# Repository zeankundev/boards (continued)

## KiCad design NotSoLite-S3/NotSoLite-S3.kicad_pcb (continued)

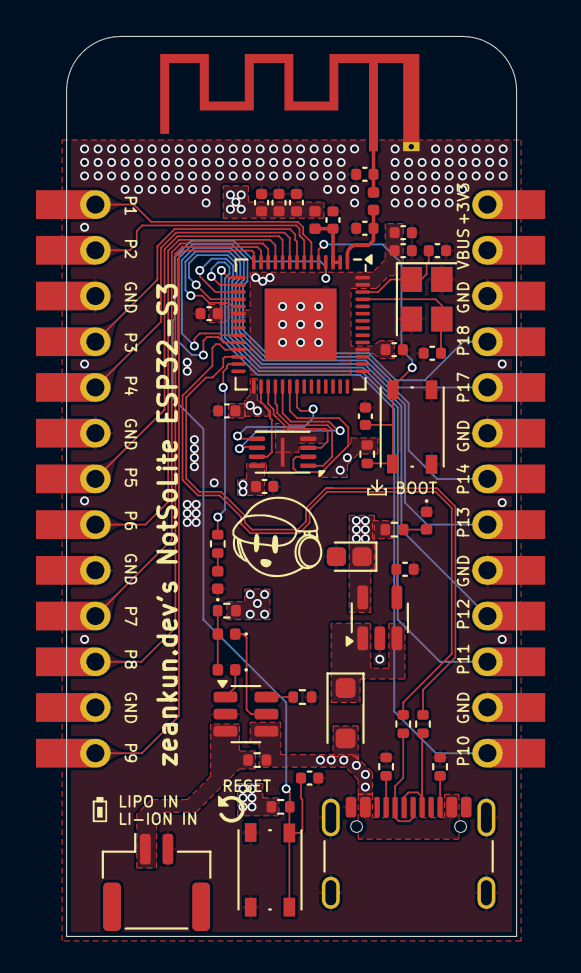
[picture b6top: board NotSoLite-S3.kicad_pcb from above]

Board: 6 copper layers, 25.0 x 50.0 mm, 48 parts (1 on the bottom side), 49 nets.

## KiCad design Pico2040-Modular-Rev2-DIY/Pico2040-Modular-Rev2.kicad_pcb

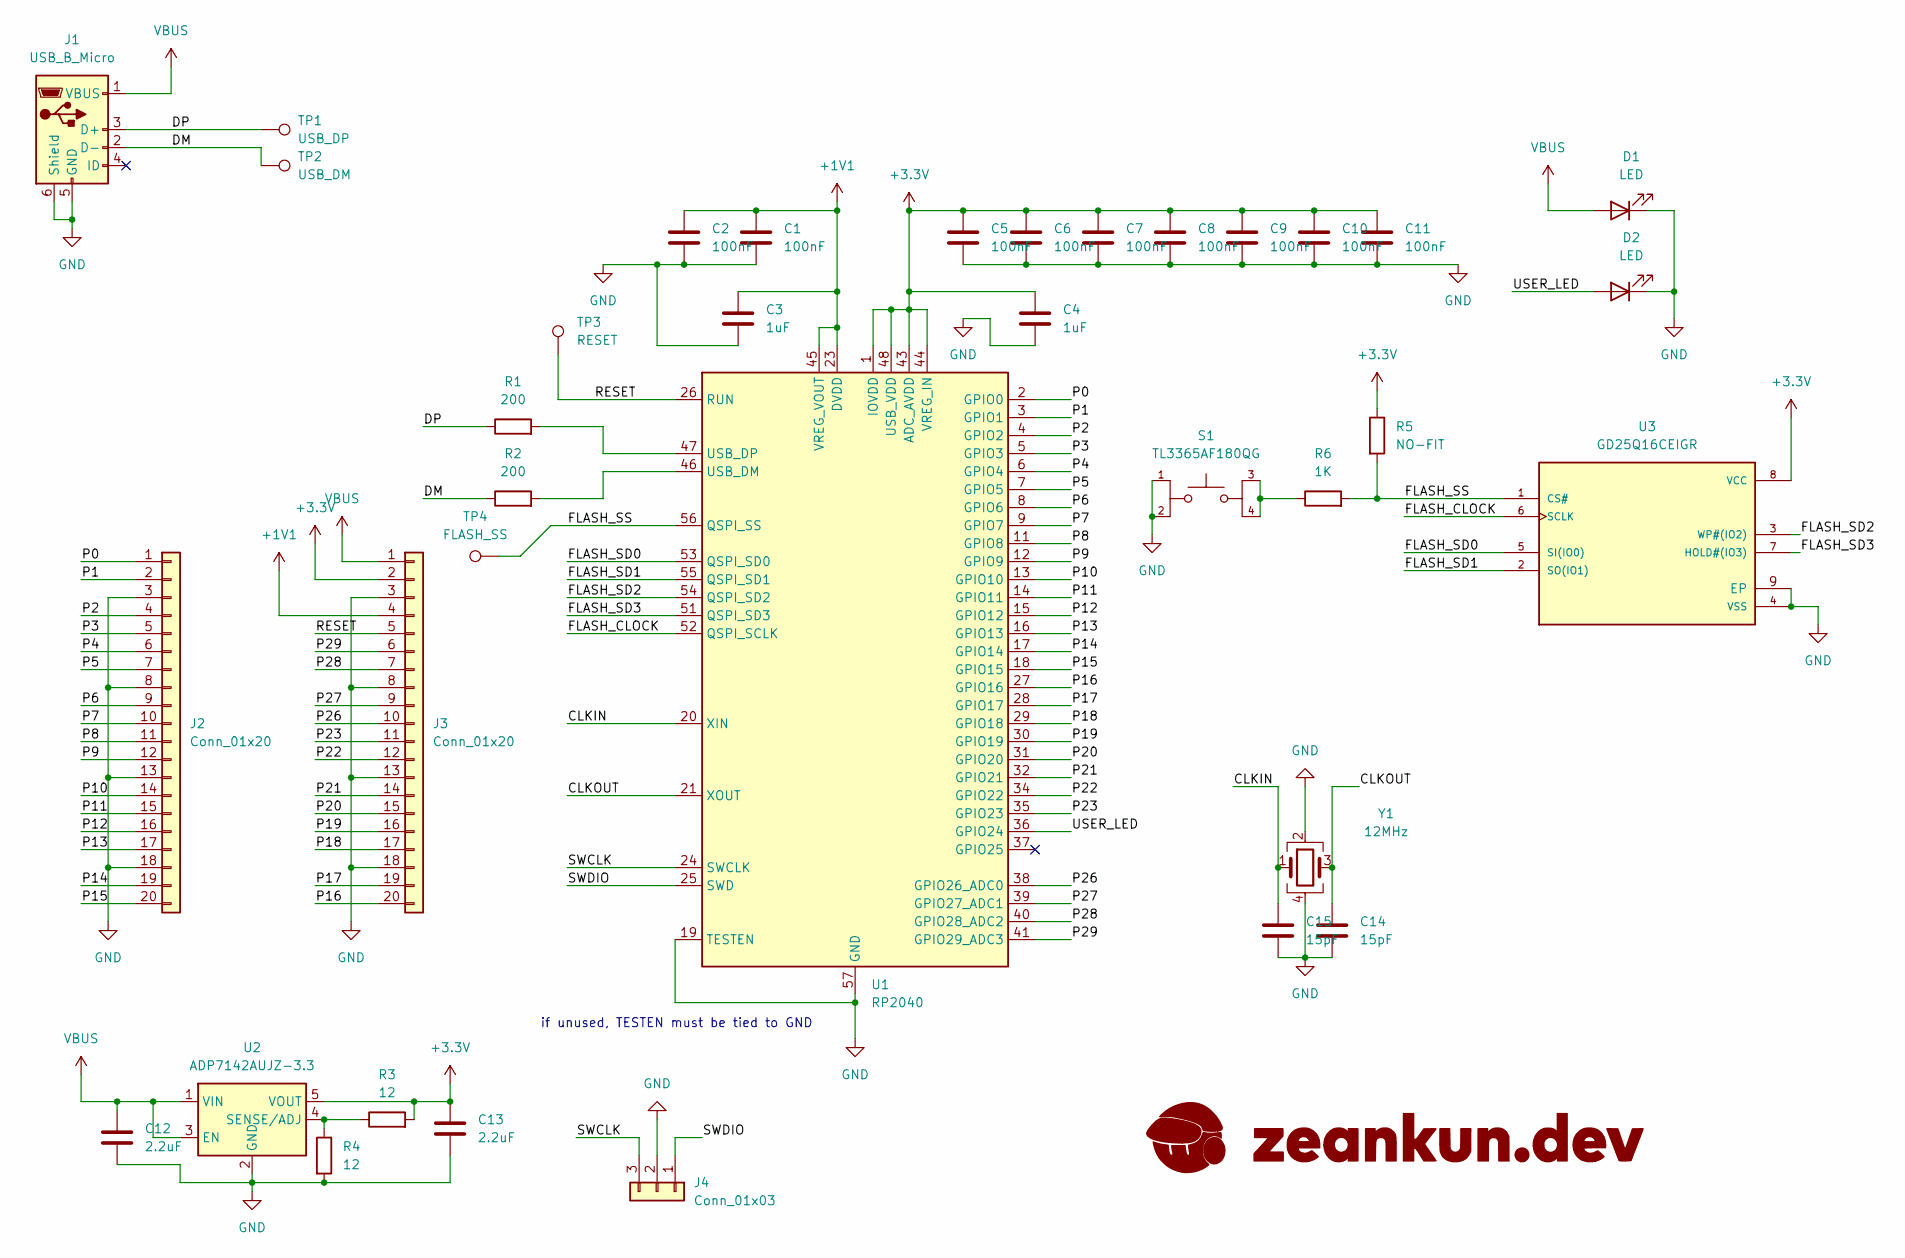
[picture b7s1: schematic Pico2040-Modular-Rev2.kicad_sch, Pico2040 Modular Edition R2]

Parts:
C1, C2, C5, C6, C7, C8, C9, C10, C11: 100nF; C_0201_0603Metric
C3, C4: 1uF; C_0201_0603Metric
C12, C13: 2.2uF; C_0201_0603Metric
C14, C15: 15pF; C_0201_0603Metric
D1, D2: LED; LED_0201_0603Metric
J1: USB_B_Micro; USB_Micro-B_Amphenol_10103594-0001LF_Horizontal
J2, J3: Conn_01x20; PinHeader_1x20_2H_P2.54mm_Vertical
J4: Conn_01x03; PinHeader_1x03_P2.54mm_Vertical
R1, R2: 200; R_0201_0603Metric
R3, R4: 12; R_0201_0603Metric
R5: NO-FIT; R_0201_0603Metric
R6: 1K; R_0201_0603Metric
S1: TL3365AF180QG; SW_TL3365AF180QG; PARTREV A
TP1: USB_DP; TestPoint_Pad_D1.0mm
TP2: USB_DM; TestPoint_Pad_D1.0mm
TP3: RESET; TestPoint_Pad_D1.0mm
TP4: FLASH_SS; TestPoint_Pad_D1.0mm
U1: RP2040; QFN-56-1EP_7x7mm_P0.4mm_EP3.2x3.2mm
U2: ADP7142AUJZ-3.3; TSOT-23-5
U3: GD25Q16CEIGR; PSON50P200X300X50-9N; PARTREV 3.0
Y1: 12MHz; Crystal_SMD_2520-4Pin_2.5x2.0mm

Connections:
+1V1: C1.1, C2.1, C3.1, J3.4, U1.23 (DVDD), U1.45 (VREG_VOUT), U1.50 (DVDD)
+3.3V: C4.1, C5.1, C6.1, C7.1, C8.1, C9.1, C10.1, C11.1, C13.1, J3.2, R3.2, R5.1, U1.1 (IOVDD), U1.10 (IOVDD), U1.22 (IOVDD), U1.33 (IOVDD), U1.42 (IOVDD), U1.43 (ADC_AVDD), U1.44 (VREG_IN), U1.48 (USB_VDD), U1.49 (IOVDD), U2.5 (VOUT), U3.8 (VCC)
/CLKIN: C15.1, U1.20 (XIN), Y1.1
/CLKOUT: C14.1, U1.21 (XOUT), Y1.3
/DM: J1.2 (D-), R2.1, TP2.1
/DP: J1.3 (D+), R1.1, TP1.1
/FLASH_CLOCK: U1.52 (QSPI_SCLK), U3.6 (SCLK)
/FLASH_SD0: U1.53 (QSPI_SD0), U3.5 (SI(IO0))
/FLASH_SD1: U1.55 (QSPI_SD1), U3.2 (SO(IO1))
/FLASH_SD2: U1.54 (QSPI_SD2), U3.3 (WP#(IO2))
/FLASH_SD3: U1.51 (QSPI_SD3), U3.7 (HOLD#(IO3))
/FLASH_SS: R5.2, R6.2, TP4.1, U1.56 (QSPI_SS), U3.1 (CS#)
/P0: J2.1, U1.2 (GPIO0)
/P1: J2.2, U1.3 (GPIO1)
/P2: J2.4, U1.4 (GPIO2)
/P3: J2.5, U1.5 (GPIO3)
/P4: J2.6, U1.6 (GPIO4)
/P5: J2.7, U1.7 (GPIO5)
/P6: J2.9, U1.8 (GPIO6)
/P7: J2.10, U1.9 (GPIO7)
/P8: J2.11, U1.11 (GPIO8)
/P9: J2.12, U1.12 (GPIO9)
/P10: J2.14, U1.13 (GPIO10)
/P11: J2.15, U1.14 (GPIO11)
/P12: J2.16, U1.15 (GPIO12)
/P13: J2.17, U1.16 (GPIO13)
/P14: J2.19, U1.17 (GPIO14)
/P15: J2.20, U1.18 (GPIO15)
/P16: J3.20, U1.27 (GPIO16)
/P17: J3.19, U1.28 (GPIO17)
/P18: J3.17, U1.29 (GPIO18)
/P19: J3.16, U1.30 (GPIO19)
/P20: J3.15, U1.31 (GPIO20)
/P21: J3.14, U1.32 (GPIO21)
/P22: J3.12, U1.34 (GPIO22)
/P23: J3.11, U1.35 (GPIO23)
/P26: J3.10, U1.38 (GPIO26_ADC0)
/P27: J3.9, U1.39 (GPIO27_ADC1)
/P28: J3.7, U1.40 (GPIO28_ADC2)
/P29: J3.6, U1.41 (GPIO29_ADC3)
/RESET: J3.5, TP3.1, U1.26 (RUN)
/SWCLK: J4.3, U1.24 (SWCLK)
/SWDIO: J4.1, U1.25 (SWD)
/USER_LED: D2.2 (A), U1.36 (GPIO24)
GND: C1.2, C2.2, C3.2, C4.2, C5.2, C6.2, C7.2, C8.2, C9.2, C10.2, C11.2, C12.2, C13.2, C14.2, C15.2, D1.1 (K), D2.1 (K), J1.5 (GND), J1.6 (Shield), J2.3, J2.8, J2.13, J2.18, J3.3, J3.8, J3.13, J3.18, J4.2, R4.2, S1.1, S1.2, U1.19 (TESTEN), U1.57 (GND), U2.2 (GND), U3.4 (VSS), U3.9 (EP), Y1.2, Y1.4
unnamed: R6.1, S1.3, S1.4
unnamed: R2.2, U1.46 (USB_DM)
unnamed: R1.2, U1.47 (USB_DP)
unnamed: R3.1, R4.1, U2.4 (SENSE/ADJ)
VBUS: C12.1, D1.2 (A), J1.1 (VBUS), J3.1, U2.1 (VIN), U2.3 (EN)

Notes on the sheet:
if unused, TESTEN must be tied to GND

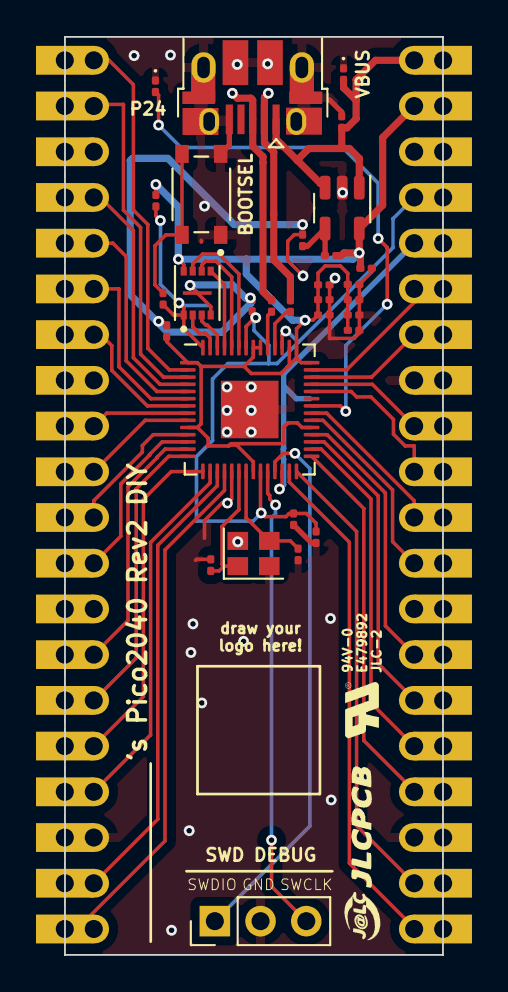
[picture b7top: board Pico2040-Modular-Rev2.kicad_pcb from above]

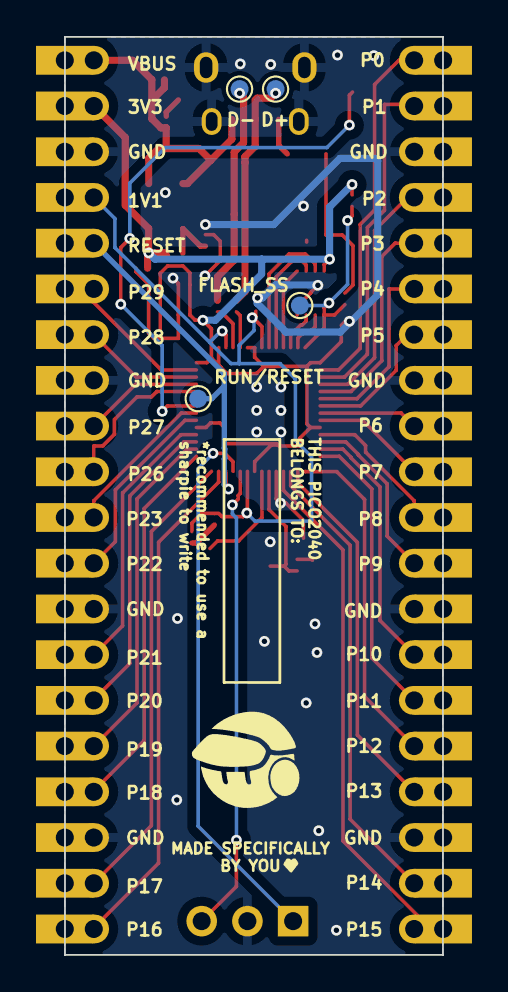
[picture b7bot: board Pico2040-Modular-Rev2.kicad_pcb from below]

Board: 2 copper layers, 21.0 x 51.0 mm, 36 parts (5 on the bottom side), 50 nets.

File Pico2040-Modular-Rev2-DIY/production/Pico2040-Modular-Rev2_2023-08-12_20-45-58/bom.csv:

Designator,Footprint,Quantity,Value,LCSC Part #
"C1, C10, C11, C2, C5, C6, C7, C8, C9",0201,9,100nF,
"C12, C13",0201,2,2.2uF,
"C14, C15",0201,2,15pF,
"C3, C4",0201,2,1uF,
"D1, D2",0201,2,LED,
J1,USB_Micro-B_Amphenol_10103594-0001LF_Horizontal,1,USB_B_Micro,
"J2, J3",PinHeader_1x20_2H_P2.54mm_Vertical,2,Conn_01x20,
J4,PinHeader_1x03_P2.54mm_Vertical,1,Conn_01x03,
"R1, R2",0201,2,200,
"R3, R4",0201,2,12,
R5,0201,1,NO-FIT,
R6,0201,1,1K,
S1,SW_TL3365AF180QG,1,TL3365AF180QG,
TP1,TestPoint_Pad_D1.0mm,1,USB_DP,
TP2,TestPoint_Pad_D1.0mm,1,USB_DM,
TP3,TestPoint_Pad_D1.0mm,1,RESET,
TP4,TestPoint_Pad_D1.0mm,1,FLASH_SS,
U1,QFN-56-1EP_7x7mm_P0.4mm_EP3.2x3.2mm,1,RP2040,
U2,TSOT-23-5,1,ADP7142AUJZ-3.3,
U3,PSON50P200X300X50-9N,1,GD25Q16CEIGR,
Y1,Crystal_SMD_2520-4Pin_2.5x2.0mm,1,12MHz,
